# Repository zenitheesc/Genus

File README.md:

<h1 align="center" style="color:white; background-color:black">Genus</h1>
<h4 align="center">Genus is a generic hardware platform aimed at instrumentation in aerospace projects. This project was developed seeking to create a set of devices which can meet the operational needs of the group Zenith EESC-USP, in a flexible, efficient and adaptive way.</h4>

<p align="center">

</p>

The project is based on the implementation of a logic bus developed by the group and named as Z-bus. The bus has the function of allowing changes in the level of processing and distribution architecture to be carried out, and that these are easy to implement. In a simplified way, the bus consists of possibilities for connecting communication protocols such as UART, I²C, SPI, and CAN, in addition to generic digital ports and some interrupt and control ports.

This bus was implemented in a main board named Genus Board. In addition to implementing the bus, this board is responsible for receiving the connection of a battery pack converting to the required voltage levels and distributing the energy.

In addition to the Genus Board, the system has modular boards which can perform dedicated processing for applications, remote control and monitoring, sensing and actuation. These boards are divided into two distinct categories, Feature Boards which are connected to the Genus Board via PCI-Express connector and are developed in a predetermined model compatible with Z-bus, and Generic Boards which can follow any development model if some compatibility requirements are used.

---

<p align="center">

</p>
<p align = "center">
<a href="zenith.eesc@gmail.com">zenith.eesc@gmail.com</a>
</p>

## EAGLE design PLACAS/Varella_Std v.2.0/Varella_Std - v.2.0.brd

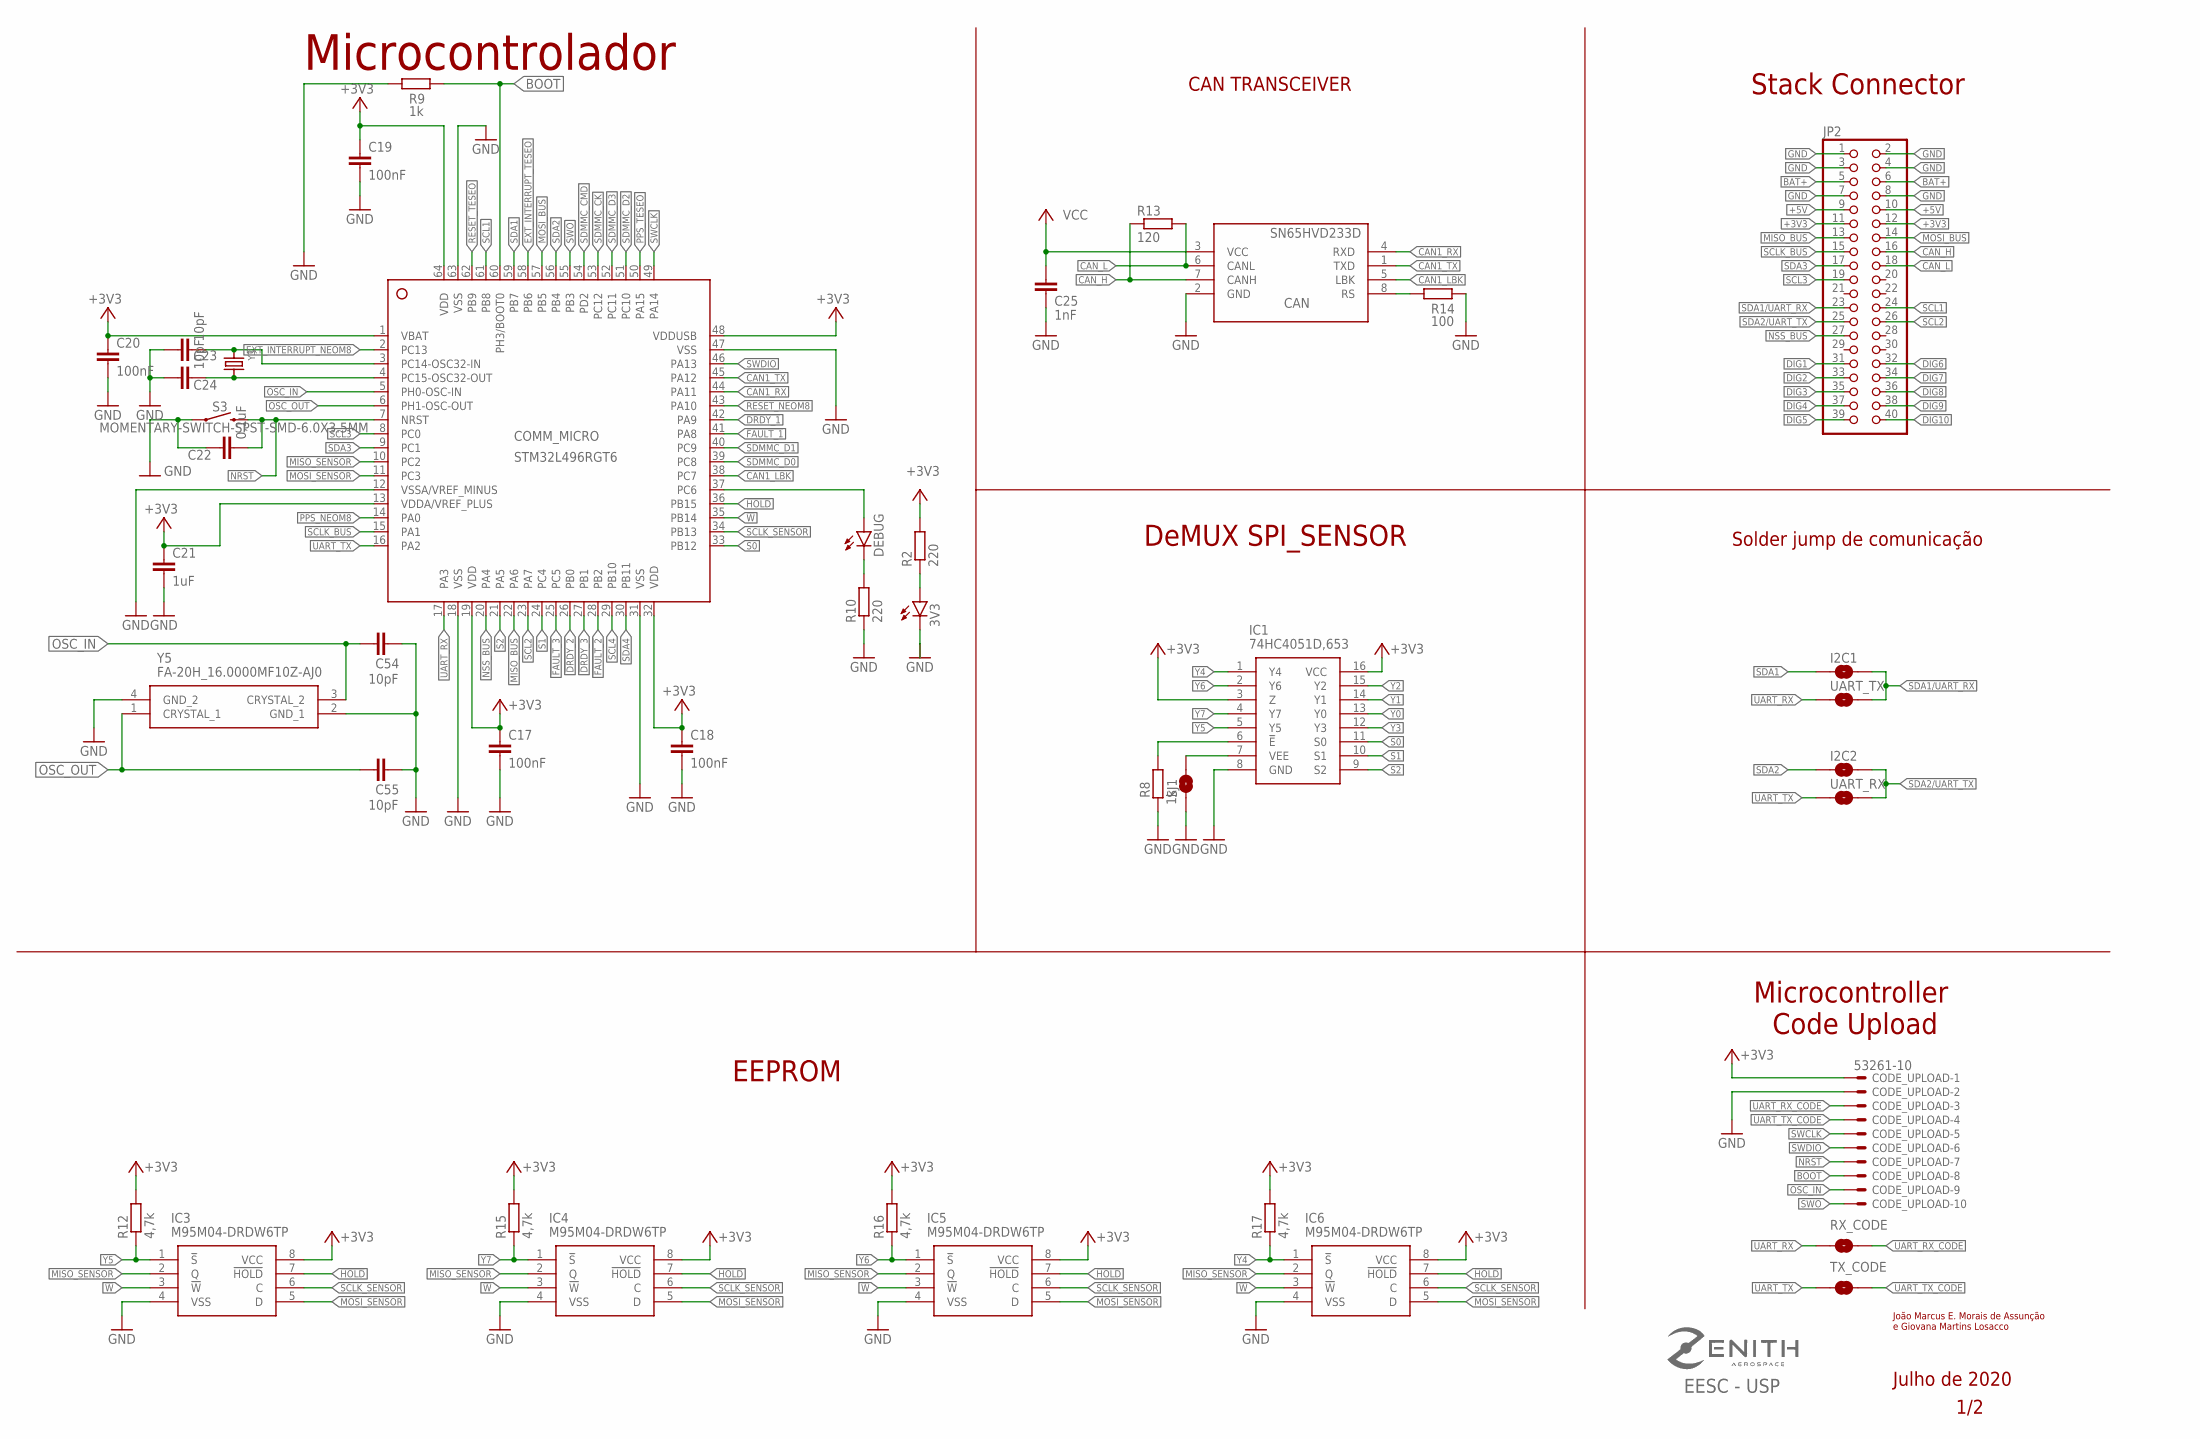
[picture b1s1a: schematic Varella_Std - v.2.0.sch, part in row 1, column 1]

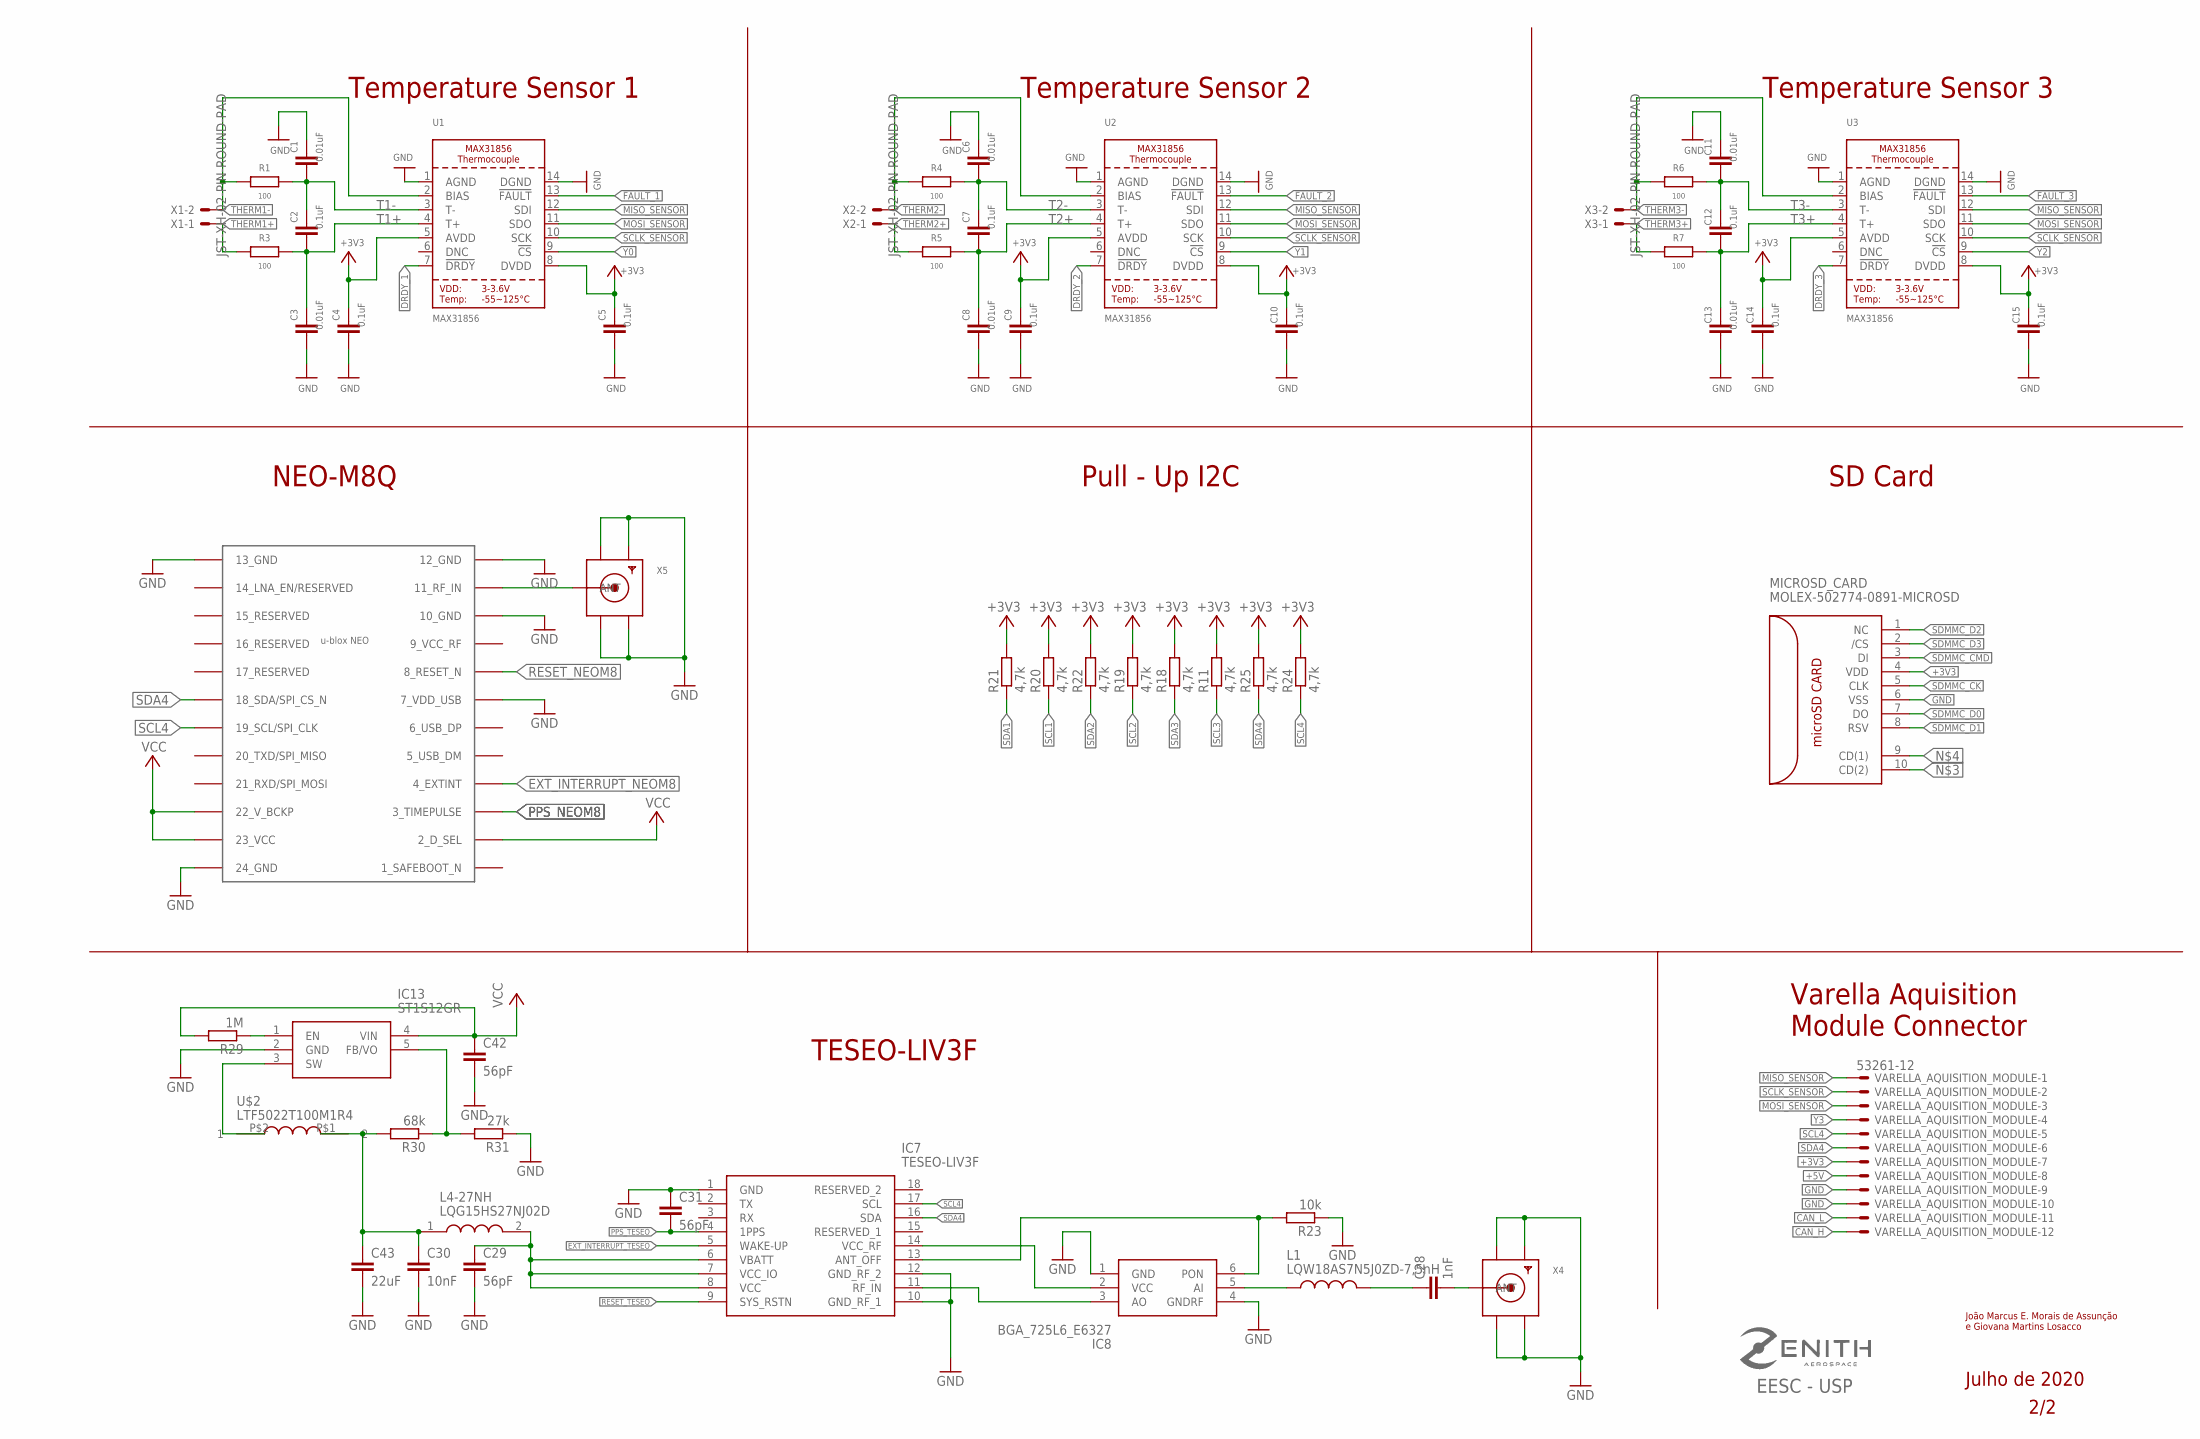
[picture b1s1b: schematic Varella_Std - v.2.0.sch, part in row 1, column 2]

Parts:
3V3: LEDCHIP-LED0805; CHIP-LED0805
C1, C3, C6, C8, C11, C13: 0.01uF; C0805
C2, C4, C5, C7, C9, C10, C12, C14, C15: 0.1uF; C0805
C17, C18, C19, C20: 100nF; C0805
C21: 1uF; C0805
C22: 0,1uF; C0805
C23, C24, C54, C55: 10pF; C0805
C25, C28: 1nF; C1206
C29, C31, C42: 56pF; C1206
C30: 10nF; C1206
C43: 22uF; C1206
CAN: SN65HVD233D; SOIC8
CODE_UPLOAD: 53261-10
COMM_MICRO: STM32L496RGT6; LQFP64_10X10
DEBUG: LEDCHIP-LED0805; CHIP-LED0805
I2C1, I2C2: SMD-JUMPER-2
IC1: 74HC4051D,653; SOIC127P600X175-16N
IC3, IC4, IC5, IC6: M95M04-DRDW6TP; SOP65P640X120-8N
IC7: TESEO-LIV3F; SON110P970X1010X230-18N
IC8: BGA_725L6_E6327; BGA725L6E6327
IC13: ST1S12GR; SOT95P280X110-5N
JP2: PINHD-2X20; 2X20
L1: LQW18AS7N5J0ZD-7,5nH; INDC1608X100N
L4-27NH: LQG15HS27NJ02D; LQG15WH0N7B02D
MICROSD_CARD: MOLEX-502774-0891-MICROSD
R1, R3, R4, R5, R6, R7, R14: 100; R0805
R2, R10: 220; R0805
R8, R9: 1k; R0805
R11, R12, R15, R16, R17, R18, R19, R20, R21, R22, R24, R25: 4,7k; R0805
R13: 120; R1206
R23: 10k; M1206
R29: 1M; M1206
R30: 68k; M1206
R31: 27k; M1206
RX_CODE: SMD-JUMPER-2
S3: MOMENTARY-SWITCH-SPST-SMD-6.0X3.5MM; TACTILE_SWITCH_SMD_6.0X3.5MM
SJ1: SMD-JUMPER-2
TX_CODE: SMD-JUMPER-2
U1, U2, U3: MAX31856; TSSOP14
U$2: LTF5022T100M1R4; LTF5022T
U$3: NEO-M8
UART_RX: SMD-JUMPER-2
UART_TX: SMD-JUMPER-2
VARELLA_AQUISITION_MODULE: 53261-12
X1, X2, X3: JST-XH-02-PIN-ROUND-PAD; JST-XH-02-PACKAGE-ROUND-PAD
X4, X5: SMACONNECTOR; SMA90_DIP
Y3: CRYSTAL8X3.8SMT; CRYSTAL_8X3.8
Y5: FA-20H_16.0000MF10Z-AJ0; FA20H160000MF12ZAC3

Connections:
!DRDY_1: COMM_MICRO.42 (PA9), U1.7 (!DRDY)
!DRDY_2: COMM_MICRO.26 (PB0), U2.7 (!DRDY)
!DRDY_3: COMM_MICRO.27 (PB1), U3.7 (!DRDY)
!FAULT_1: COMM_MICRO.41 (PA8), U1.13 (!FAULT)
!FAULT_2: COMM_MICRO.28 (PB2), U2.13 (!FAULT)
!FAULT_3: COMM_MICRO.25 (PC5), U3.13 (!FAULT)
!HOLD: COMM_MICRO.36 (PB15), IC3.7 (!HOLD), IC4.7 (!HOLD), IC5.7 (!HOLD), IC6.7 (!HOLD)
!W: COMM_MICRO.35 (PB14), IC3.3 (!W), IC4.3 (!W), IC5.3 (!W), IC6.3 (!W)
+3V3: C4.1, C5.1, C9.1, C10.1, C14.1, C15.1, C17.1, C18.1, C19.1, C20.1, C21.1, C25.1, C42.1, CAN.3 (VCC), CODE_UPLOAD.1, COMM_MICRO.1 (VBAT), COMM_MICRO.13 (VDDA/VREF_PLUS), COMM_MICRO.19 (VDD), COMM_MICRO.32 (VDD), COMM_MICRO.48 (VDDUSB), COMM_MICRO.64 (VDD), IC1.3 (Z), IC1.16 (VCC), IC3.8 (VCC), IC4.8 (VCC), IC5.8 (VCC), IC6.8 (VCC), IC13.4 (VIN), JP2.11, JP2.12, MICROSD_CARD.4 (VDD), R2.2, R11.2, R12.2, R15.2, R16.2, R17.2, R18.2, R19.2, R20.2, R21.1, R22.1, R24.2, R25.2, R29.2, U1.5 (AVDD), U1.8 (DVDD), U2.5 (AVDD), U2.8 (DVDD), U3.5 (AVDD), U3.8 (DVDD), U$3.2 (2_D_SEL), U$3.22 (22_V_BCKP), U$3.23 (23_VCC), VARELLA_AQUISITION_MODULE.7
+5V: JP2.9, JP2.10, VARELLA_AQUISITION_MODULE.8
BAT+: JP2.5, JP2.6
BOOT: CODE_UPLOAD.8, COMM_MICRO.60 (PH3/BOOT0), R9.1
CAN1_LBK: CAN.5 (LBK), COMM_MICRO.38 (PC7)
CAN1_RX: CAN.4 (RXD), COMM_MICRO.44 (PA11)
CAN1_TX: CAN.1 (TXD), COMM_MICRO.45 (PA12)
CAN_H: CAN.7 (CANH), JP2.16, R13.1, VARELLA_AQUISITION_MODULE.12
CAN_L: CAN.6 (CANL), JP2.18, R13.2, VARELLA_AQUISITION_MODULE.11
DIG1: JP2.31
DIG2: JP2.33
DIG3: JP2.35
DIG4: JP2.37
DIG5: JP2.39
DIG6: JP2.32
DIG7: JP2.34
DIG8: JP2.36
DIG9: JP2.38
DIG10: JP2.40
EXT_INTERRUPT_NEOM8: COMM_MICRO.2 (PC13), U$3.4 (4_EXTINT)
EXT_INTERRUPT_TESEO: COMM_MICRO.58 (PB6), IC7.5 (WAKE-UP)
GND: 3V3.C, C1.1, C3.2, C4.2, C5.2, C6.1, C8.2, C9.2, C10.2, C11.1, C13.2, C14.2, C15.2, C17.2, C18.2, C19.2, C20.2, C21.2, C22.1, C23.1, C24.1, C25.2, C29.2, C30.2, C31.1, C42.2, C43.2, C54.2, C55.2, CAN.2 (GND), CODE_UPLOAD.2, COMM_MICRO.12 (VSSA/VREF_MINUS), COMM_MICRO.18 (VSS), COMM_MICRO.31 (VSS), COMM_MICRO.47 (VSS), COMM_MICRO.63 (VSS), IC1.8 (GND), IC3.4 (VSS), IC4.4 (VSS), IC5.4 (VSS), IC6.4 (VSS), IC7.1 (GND), IC7.10 (GND_RF_1), IC7.12 (GND_RF_2), IC8.1 (GND), IC8.4 (GNDRF), IC13.2 (GND), JP2.1, JP2.2, JP2.3, JP2.4, JP2.7, JP2.8, MICROSD_CARD.6 (VSS), R8.1, R9.2, R10.1, R14.1, R23.1, R31.1, S3.1, SJ1.2, U1.1 (AGND), U1.14 (DGND), U2.1 (AGND), U2.14 (DGND), U3.1 (AGND), U3.14 (DGND), U$3.7 (7_VDD_USB), U$3.10 (10_GND), U$3.12 (12_GND), U$3.13 (13_GND), U$3.24 (24_GND), VARELLA_AQUISITION_MODULE.9, VARELLA_AQUISITION_MODULE.10, X4.GND1, X4.GND2, X4.GND3, X4.GND4, X5.GND1, X5.GND2, X5.GND3, X5.GND4, Y5.2 (GND_1), Y5.4 (GND_2)
L3: 3V3.A, R2.1
MISO_BUS: COMM_MICRO.22 (PA6), JP2.13
MISO_SENSOR: COMM_MICRO.10 (PC2), IC3.2 (Q), IC4.2 (Q), IC5.2 (Q), IC6.2 (Q), U1.12 (SDI), U2.12 (SDI), U3.12 (SDI), VARELLA_AQUISITION_MODULE.1
MOSI_BUS: COMM_MICRO.57 (PB5), JP2.14
MOSI_SENSOR: COMM_MICRO.11 (PC3), IC3.5 (D), IC4.5 (D), IC5.5 (D), IC6.5 (D), U1.11 (SDO), U2.11 (SDO), U3.11 (SDO), VARELLA_AQUISITION_MODULE.3
unnamed: IC1.7 (VEE), SJ1.1
unnamed: U$3.11 (11_RF_IN), X5.ANTENNA (ANT)
unnamed: C29.1, IC7.6 (VBATT), IC7.7 (VCC_IO), IC7.8 (VCC), L4-27NH.2
unnamed: IC7.14 (VCC_RF), IC8.2 (VCC)
unnamed: IC1.6 (!E), R8.2
unnamed: C28.2, X4.ANTENNA (ANT)
unnamed: COMM_MICRO.37 (PC6), DEBUG.A
unnamed: DEBUG.C, R10.2
unnamed: C23.2, COMM_MICRO.3 (PC14-OSC32-IN), Y3.P$1 (1)
unnamed: C24.2, COMM_MICRO.4 (PC15-OSC32-OUT), Y3.P$4 (2)
unnamed: IC7.11 (RF_IN), IC8.3 (AO)
unnamed: IC7.13 (ANT_OFF), IC8.6 (PON), R23.2
unnamed: CAN.8 (RS), R14.2
unnamed: C28.1, L1.2
unnamed: IC8.5 (AI), L1.1
unnamed: IC13.1 (EN), R29.1
unnamed: IC13.3 (SW), U$2.P$2 (1)
unnamed: IC13.5 (FB/VO), R30.1, R31.2
NRST: C22.2, CODE_UPLOAD.7, COMM_MICRO.7 (NRST), S3.2
NSS_BUS: COMM_MICRO.20 (PA4), JP2.27
OSC_IN: C54.1, CODE_UPLOAD.9, COMM_MICRO.5 (PH0-OSC-IN), Y5.3 (CRYSTAL_2)
OSC_OUT: C55.1, COMM_MICRO.6 (PH1-OSC-OUT), Y5.1 (CRYSTAL_1)
PPS_NEOM8: COMM_MICRO.14 (PA0), U$3.3 (3_TIMEPULSE)
PPS_TESEO: C31.2, COMM_MICRO.50 (PA15), IC7.4 (1PPS)
RESET_NEOM8: COMM_MICRO.43 (PA10), U$3.8 (8_RESET_N)
RESET_TESEO: COMM_MICRO.62 (PB9), IC7.9 (SYS_RSTN)
S0: COMM_MICRO.33 (PB12), IC1.11 (S0)
S1: COMM_MICRO.24 (PC4), IC1.10 (S1)
S2: COMM_MICRO.21 (PA5), IC1.9 (S2)
SCL1: COMM_MICRO.61 (PB8), JP2.24, R20.1
SCL2: COMM_MICRO.23 (PA7), JP2.26, R19.1
SCL3: COMM_MICRO.8 (PC0), JP2.19, R11.1
SCL4: COMM_MICRO.29 (PB10), IC7.17 (SCL), R24.1, U$3.19 (19_SCL/SPI_CLK), VARELLA_AQUISITION_MODULE.5
SCLK_BUS: COMM_MICRO.15 (PA1), JP2.15
SCLK_SENSOR: COMM_MICRO.34 (PB13), IC3.6 (C), IC4.6 (C), IC5.6 (C), IC6.6 (C), U1.10 (SCK), U2.10 (SCK), U3.10 (SCK), VARELLA_AQUISITION_MODULE.2
SDA1: COMM_MICRO.59 (PB7), I2C1.2, R21.2
SDA1/UART_RX: I2C1.1, JP2.23, UART_TX.1
SDA2: COMM_MICRO.56 (PB4), I2C2.2, R22.2
SDA2/UART_TX: I2C2.1, JP2.25, UART_RX.1
SDA3: COMM_MICRO.9 (PC1), JP2.17, R18.1
SDA4: COMM_MICRO.30 (PB11), IC7.16 (SDA), R25.1, U$3.18 (18_SDA/SPI_CS_N), VARELLA_AQUISITION_MODULE.6
SDMMC_CK: COMM_MICRO.53 (PC12), MICROSD_CARD.5 (CLK)
SDMMC_CMD: COMM_MICRO.54 (PD2), MICROSD_CARD.3 (DI)
SDMMC_D0: COMM_MICRO.39 (PC8), MICROSD_CARD.7 (DO)
SDMMC_D1: COMM_MICRO.40 (PC9), MICROSD_CARD.8 (RSV)
SDMMC_D2: COMM_MICRO.51 (PC10), MICROSD_CARD.1 (NC)
SDMMC_D3: COMM_MICRO.52 (PC11), MICROSD_CARD.2 (/CS)
SWCLK: CODE_UPLOAD.5, COMM_MICRO.49 (PA14)
SWDIO: CODE_UPLOAD.6, COMM_MICRO.46 (PA13)
SWO: CODE_UPLOAD.10, COMM_MICRO.55 (PB3)
T1+: C2.2, C3.1, R3.2, U1.4 (T+)
T1-: C1.2, C2.1, R1.2, U1.3 (T-)
T2+: C7.2, C8.1, R5.2, U2.4 (T+)
T2-: C6.2, C7.1, R4.2, U2.3 (T-)
T3+: C12.2, C13.1, R7.2, U3.4 (T+)
T3-: C11.2, C12.1, R6.2, U3.3 (T-)
TESEO3: C30.1, C43.1, L4-27NH.1, R30.2, U$2.P$1 (2)
THERM1+: R3.1, X1.1
THERM1-: R1.1, U1.2 (BIAS), X1.2
THERM2+: R5.1, X2.1
THERM2-: R4.1, U2.2 (BIAS), X2.2
THERM3+: R7.1, X3.1
THERM3-: R6.1, U3.2 (BIAS), X3.2
UART_RX: COMM_MICRO.17 (PA3), RX_CODE.1, UART_TX.2
UART_RX_CODE: CODE_UPLOAD.3, RX_CODE.2
UART_TX: COMM_MICRO.16 (PA2), TX_CODE.1, UART_RX.2
UART_TX_CODE: CODE_UPLOAD.4, TX_CODE.2
Y0: IC1.13 (Y0), U1.9 (!CS)
Y1: IC1.14 (Y1), U2.9 (!CS)
Y2: IC1.15 (Y2), U3.9 (!CS)
Y3: IC1.12 (Y3), VARELLA_AQUISITION_MODULE.4
Y4: IC1.1 (Y4), IC6.1 (!S), R17.1
Y5: IC1.5 (Y5), IC3.1 (!S), R12.1
Y6: IC1.2 (Y6), IC5.1 (!S), R16.1
Y7: IC1.4 (Y7), IC4.1 (!S), R15.1

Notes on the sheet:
Microcontroller Code Upload
Varella Aquisition Module Connector
Stack Connector
SD Card
Microcontrolador
CAN TRANSCEIVER
Temperature Sensor 2
Temperature Sensor 3
Temperature Sensor 1
Solder jump de comunicação
DeMUX SPI_SENSOR
EEPROM
NEO-M8Q
TESEO-LIV3F
Pull - Up I2C
EESC - USP
João Marcus E. Morais de Assunção e Giovana Martins Losacco
Julho de 2020
1/2
2/2

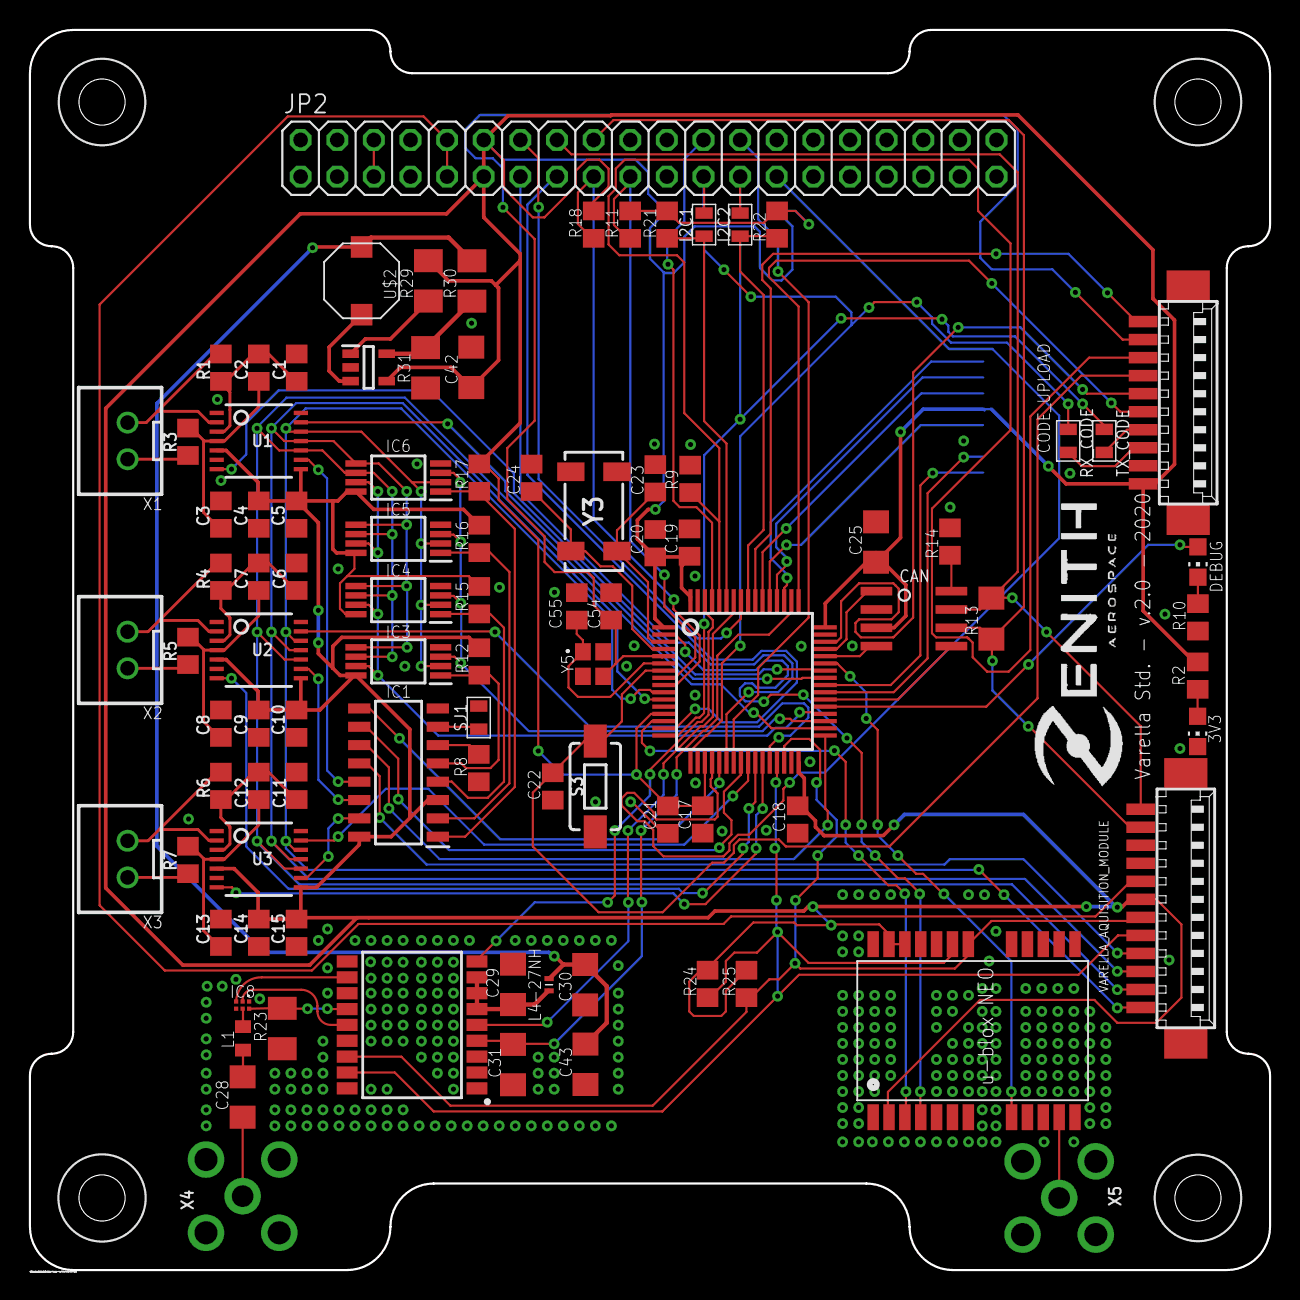
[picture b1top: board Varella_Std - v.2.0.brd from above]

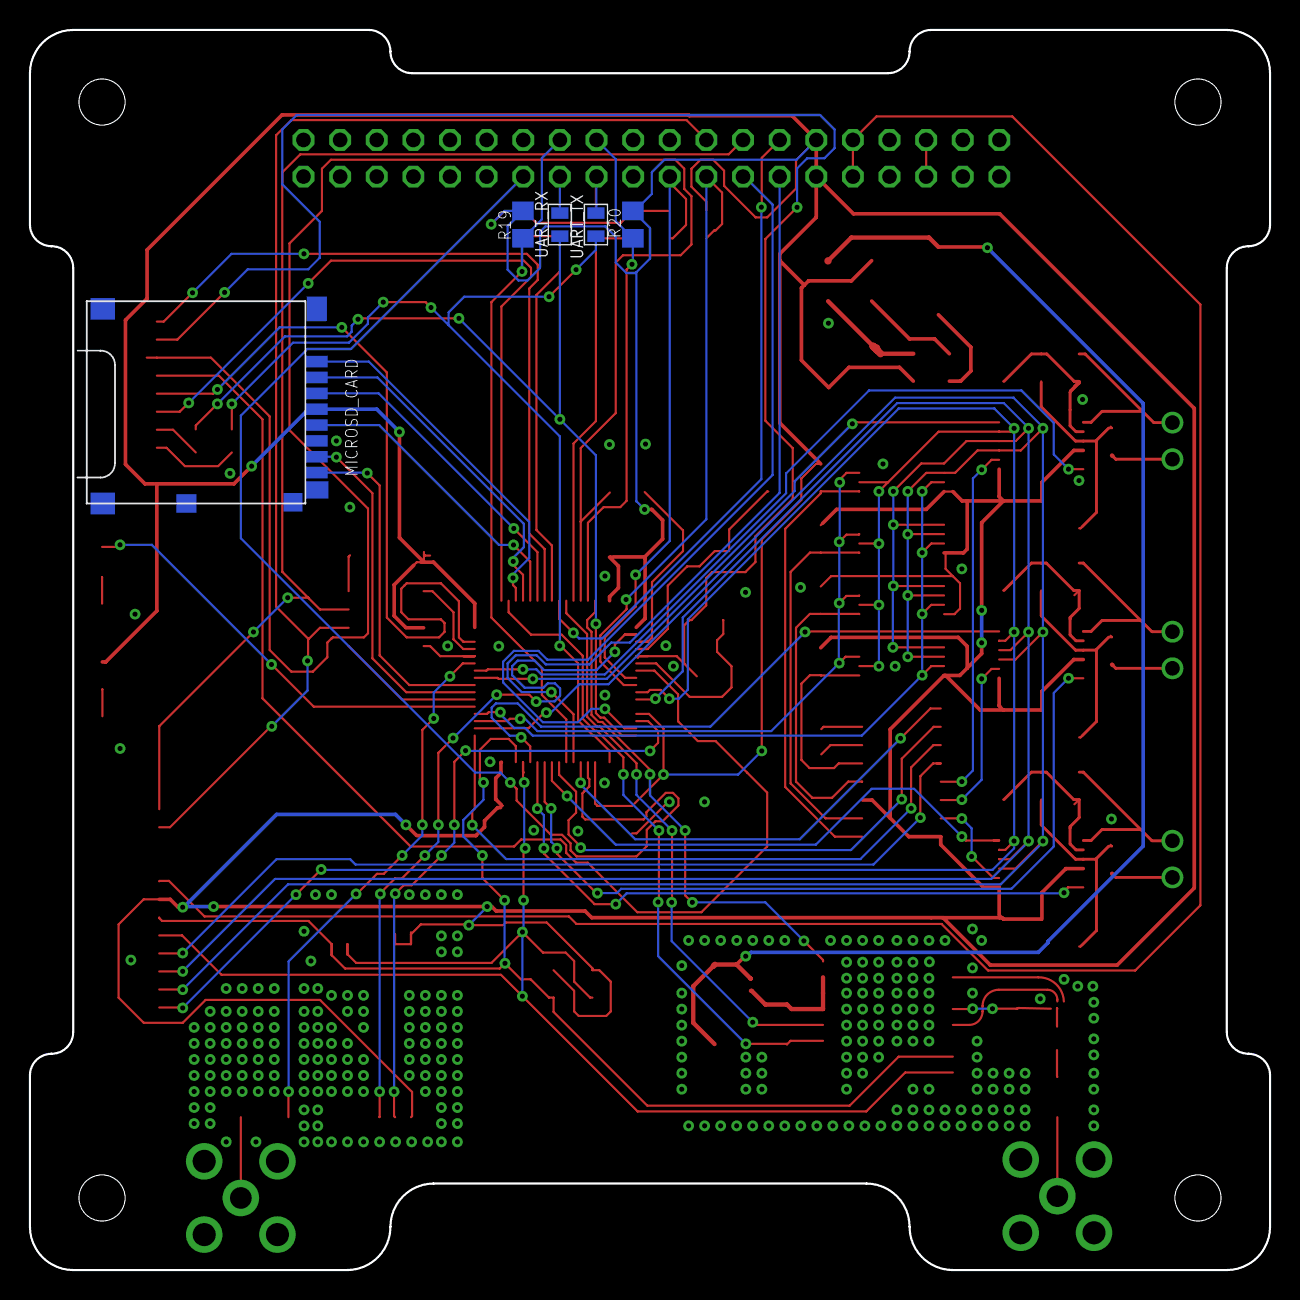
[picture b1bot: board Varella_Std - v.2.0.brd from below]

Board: 2 copper layers, 86.0 x 86.0 mm, 98 parts (5 on the bottom side), 100 nets.

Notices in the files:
parts and their libraries:
COPYRIGHT: Copyright (C) 2018 Accelerated Designs. All rights reserved
SparkFun-Switches: Licensing: Creative Commons ShareAlike 4.0 International - https://creativecommons.org/licenses/by-sa/4.0
FaBo-PIN: Released under the Creative Commons Attribution-ShareAlike 4.0 License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
